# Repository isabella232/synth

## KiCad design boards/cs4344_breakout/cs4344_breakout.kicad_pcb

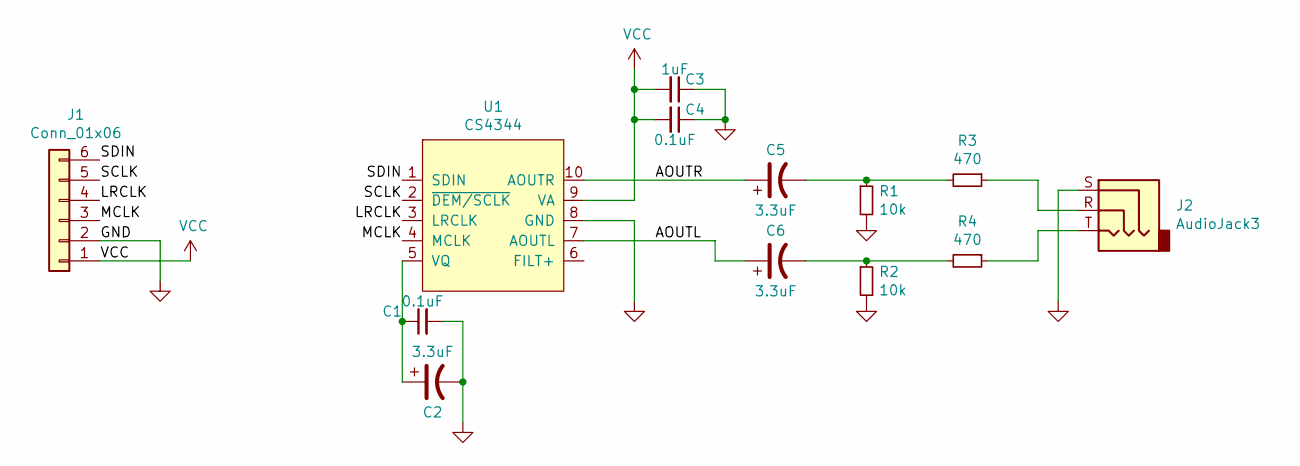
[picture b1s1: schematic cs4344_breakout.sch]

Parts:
C1, C4: 0.1uF; C_0603_1608Metric_Pad1.05x0.95mm_HandSolder
C2, C5, C6: 3.3uF; CP_EIA-1608-08_AVX-J_Pad1.25x1.05mm_HandSolder
C3: 1uF; C_0603_1608Metric_Pad1.05x0.95mm_HandSolder
J1: Conn_01x06; PinHeader_1x06_P2.54mm_Vertical
J2: AudioJack3; Jack_3.5mm_CUI_SJ-3523-SMT_Horizontal
R1, R2: 10k; R_0603_1608Metric_Pad1.05x0.95mm_HandSolder
R3, R4: 470; R_0603_1608Metric_Pad1.05x0.95mm_HandSolder
U1: CS4344; TSSOP-10_3x3mm_P0.5mm

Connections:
/AOUTL: C6.1, U1.7 (AOUTL)
/AOUTR: C5.1, U1.10 (AOUTR)
/LRCLK: J1.4, U1.3 (LRCLK)
/MCLK: J1.3, U1.4 (MCLK)
/SCLK: J1.5, U1.2 (~DEM/SCLK)
/SDIN: J1.6, U1.1 (SDIN)
GND: C1.2, C2.2, C3.1, C4.1, J1.2, J2.S, R1.2, R2.2, U1.8 (GND)
unnamed: C1.1, C2.1, U1.5 (VQ)
unnamed: C5.2, R1.1, R3.2
unnamed: C6.2, R2.1, R4.2
unnamed: J2.R, R3.1
unnamed: J2.T, R4.1
VCC: C3.2, C4.2, J1.1, U1.9 (VA)

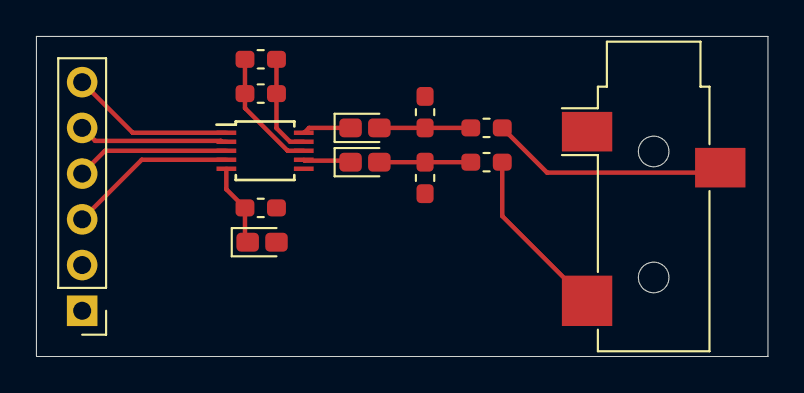
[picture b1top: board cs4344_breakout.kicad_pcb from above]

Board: 2 copper layers, 40.6 x 17.8 mm, 13 parts (0 on the bottom side), 13 nets.

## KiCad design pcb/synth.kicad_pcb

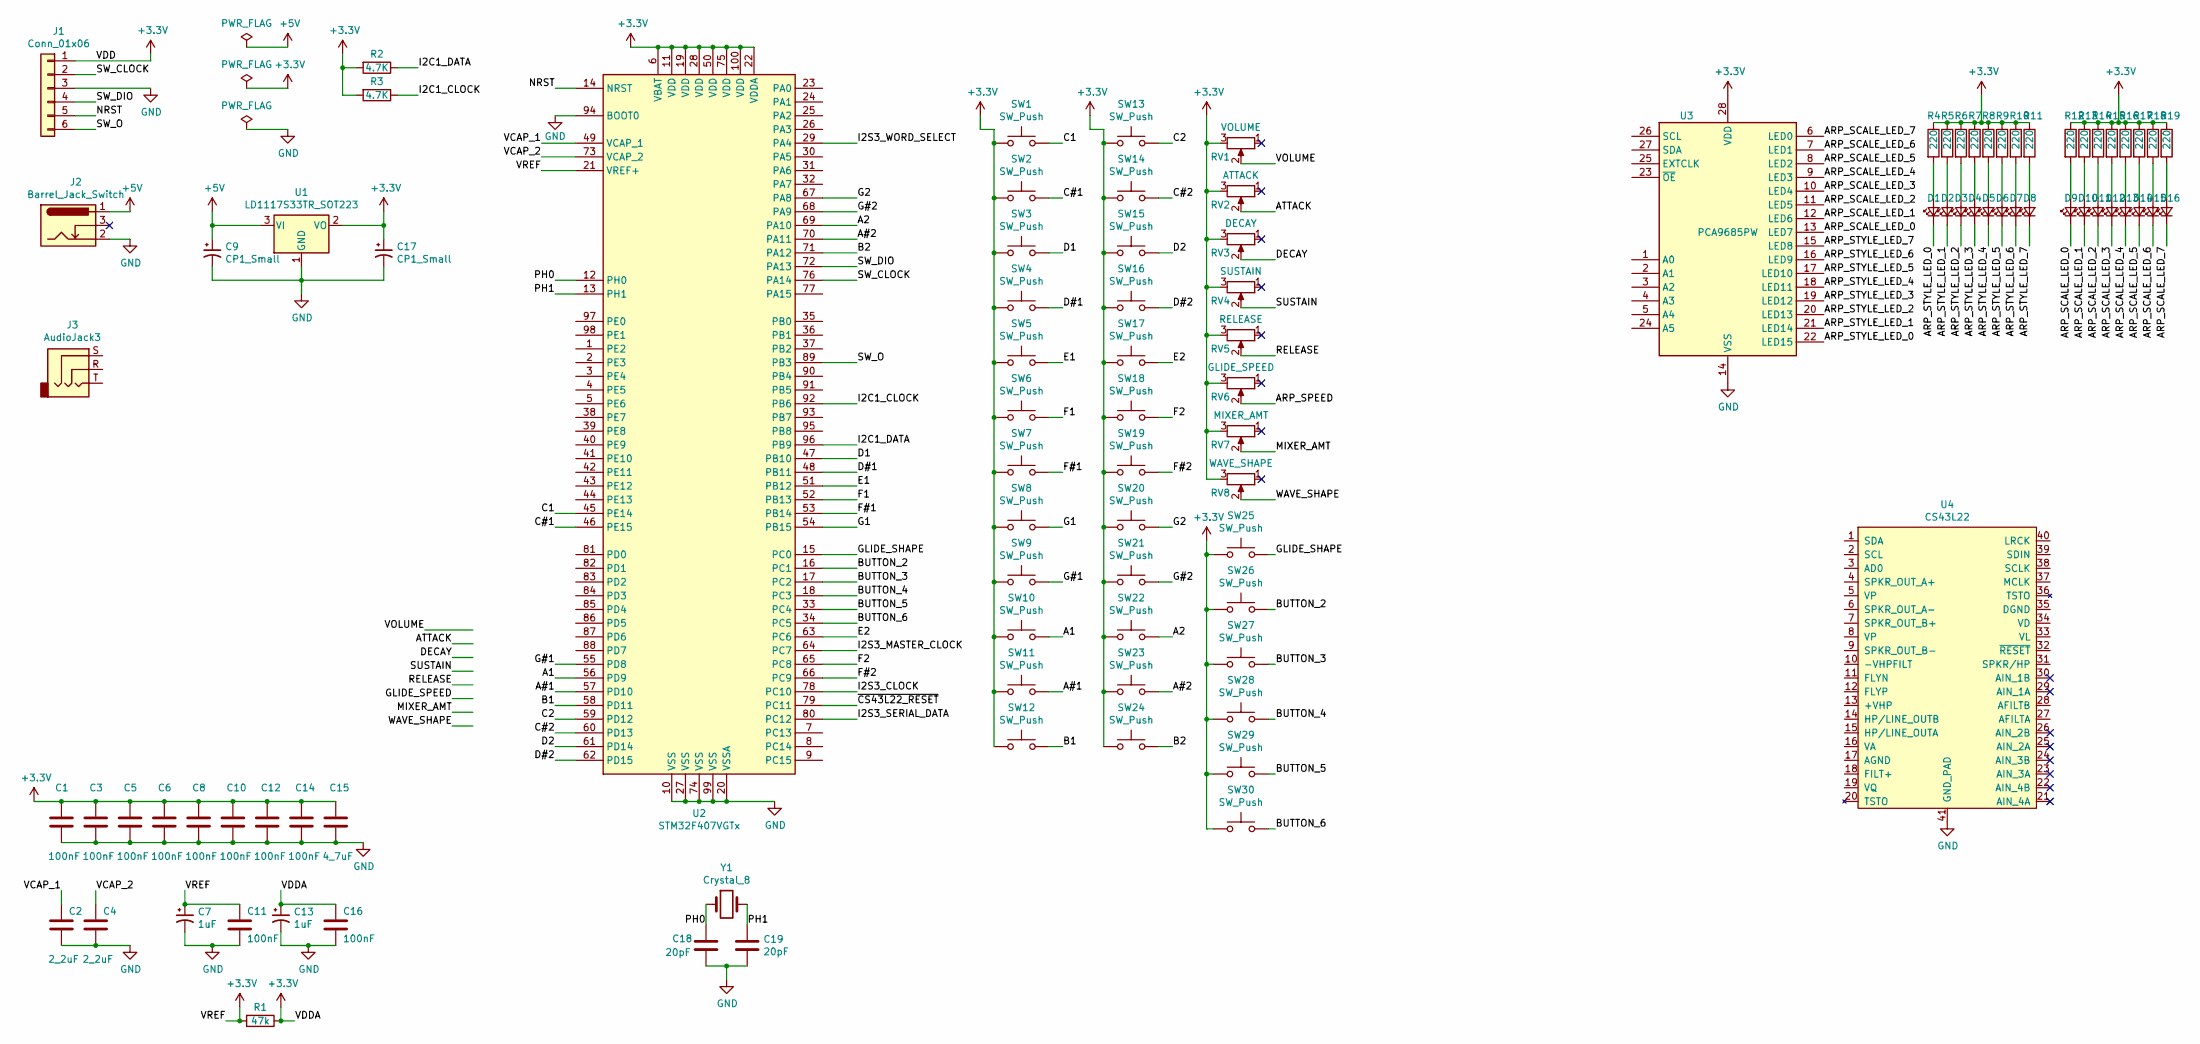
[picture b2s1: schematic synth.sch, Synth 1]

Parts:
C1, C3, C5, C6, C8, C10, C11, C12, C14, C16: 100nF; C_Disc_D3.0mm_W2.0mm_P2.50mm
C2, C4: 2_2uF; C_Disc_D3.0mm_W2.0mm_P2.50mm
C7, C13: 1uF; C_Disc_D3.0mm_W2.0mm_P2.50mm
C9, C17: CP1_Small
C15: 4_7uF; C_Disc_D3.0mm_W2.0mm_P2.50mm
C18, C19: 20pF; C_Disc_D3.0mm_W2.0mm_P2.50mm
D1, D2, D3, D4, D5, D6, D7, D8, D9, D10, D11, D12, D13, D14, D15, D16: LED_Small; LED_0805_2012Metric
J1: Conn_01x06; PinHeader_1x06_P2.54mm_Vertical
J2: Barrel_Jack_Switch; BarrelJack_CUI_PJ-063AH_Horizontal
J3: AudioJack3; Jack_3.5mm_CUI_SJ1-3533NG_Horizontal
R1: 47k
R2, R3: 4.7K; R_Axial_DIN0204_L3.6mm_D1.6mm_P5.08mm_Horizontal
R4, R5, R6, R7, R8, R9, R10, R11, R12, R13, R14, R15, R16, R17, R18, R19: 220; R_0805_2012Metric
RV1: VOLUME; Potentiometer_Bourns_PTV09A-1_Single_Vertical
RV2: ATTACK; Potentiometer_Bourns_PTV09A-1_Single_Vertical
RV3: DECAY; Potentiometer_Bourns_PTV09A-1_Single_Vertical
RV4: SUSTAIN; Potentiometer_Bourns_PTV09A-1_Single_Vertical
RV5: RELEASE; Potentiometer_Bourns_PTV09A-1_Single_Vertical
RV6: GLIDE_SPEED; Potentiometer_Bourns_PTV09A-1_Single_Vertical
RV7: MIXER_AMT; Potentiometer_Bourns_PTV09A-1_Single_Vertical
RV8: WAVE_SHAPE; Potentiometer_Bourns_PTV09A-1_Single_Vertical
SW1, SW2, SW3, SW4, SW5, SW6, SW7, SW8, SW9, SW10, SW11, SW12, SW13, SW14, SW15, SW16, SW17, SW18, SW19, SW20, SW21, SW22, SW23, SW24, SW25, SW26, SW27, SW28, SW29, SW30: SW_Push; Mountain Switch Narrow
U1: LD1117S33TR_SOT223; SOT-223-3_TabPin2
U2: STM32F407VGTx; LQFP-100_14x14mm_P0.5mm
U3: PCA9685PW; TSSOP-28_4.4x9.7mm_P0.65mm
U4: CS43L22; QFN-40-1EP_6x6mm_P0.5mm_EP4.6x4.6mm
Y1: Crystal_8; ATS08A

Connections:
+3V3: C1.1, C3.1, C5.1, C6.1, C7.1, C8.1, C10.1, C11.1, C12.1, C13.1, C14.1, C15.1, C16.1, C17.1, J1.1, R1.1, R1.2, R2.2, R3.2, R4.1, R5.1, R6.1, R7.1, R8.1, R9.1, R10.1, R11.1, R12.1, R13.1, R14.1, R15.1, R16.1, R17.1, R18.1, R19.1, RV1.3, RV2.3, RV3.3, RV4.3, RV5.3, RV6.3, RV7.3, RV8.3, SW1.1, SW2.1, SW3.1, SW4.1, SW5.1, SW6.1, SW7.1, SW8.1, SW9.1, SW10.1, SW11.1, SW12.1, SW13.1, SW14.1, SW15.1, SW16.1, SW17.1, SW18.1, SW19.1, SW20.1, SW21.1, SW22.1, SW23.1, SW24.1, SW25.1, SW26.1, SW27.1, SW28.1, SW29.1, SW30.1, U1.2 (VO), U2.6 (VBAT), U2.11 (VDD), U2.19 (VDD), U2.21 (VREF+), U2.22 (VDDA), U2.28 (VDD), U2.50 (VDD), U2.75 (VDD), U2.100 (VDD), U3.28 (VDD)
+5V: C9.1, J2.1, U1.3 (VI)
/A1: SW10.2, U2.56 (PD9)
/A2: SW22.2, U2.69 (PA10)
/A#1: SW11.2, U2.57 (PD10)
/A#2: SW23.2, U2.70 (PA11)
/ARP_SCALE_LED_0: D9.1 (K), U3.13 (LED7)
/ARP_SCALE_LED_1: D10.1 (K), U3.12 (LED6)
/ARP_SCALE_LED_2: D11.1 (K), U3.11 (LED5)
/ARP_SCALE_LED_3: D12.1 (K), U3.10 (LED4)
/ARP_SCALE_LED_4: D13.1 (K), U3.9 (LED3)
/ARP_SCALE_LED_5: D14.1 (K), U3.8 (LED2)
/ARP_SCALE_LED_6: D15.1 (K), U3.7 (LED1)
/ARP_SCALE_LED_7: D16.1 (K), U3.6 (LED0)
/ARP_SPEED: RV6.2
/ARP_STYLE_LED_0: D1.1 (K), U3.22 (LED15)
/ARP_STYLE_LED_1: D2.1 (K), U3.21 (LED14)
/ARP_STYLE_LED_2: D3.1 (K), U3.20 (LED13)
/ARP_STYLE_LED_3: D4.1 (K), U3.19 (LED12)
/ARP_STYLE_LED_4: D5.1 (K), U3.18 (LED11)
/ARP_STYLE_LED_5: D6.1 (K), U3.17 (LED10)
/ARP_STYLE_LED_6: D7.1 (K), U3.16 (LED9)
/ARP_STYLE_LED_7: D8.1 (K), U3.15 (LED8)
/ATTACK: RV2.2
/B1: SW12.2, U2.58 (PD11)
/B2: SW24.2, U2.71 (PA12)
/BUTTON_2: SW26.2, U2.16 (PC1)
/BUTTON_3: SW27.2, U2.17 (PC2)
/BUTTON_4: SW28.2, U2.18 (PC3)
/BUTTON_5: SW29.2, U2.33 (PC4)
/BUTTON_6: SW30.2, U2.34 (PC5)
/C1: SW1.2, U2.45 (PE14)
/C2: SW13.2, U2.59 (PD12)
/C#1: SW2.2, U2.46 (PE15)
/C#2: SW14.2, U2.60 (PD13)
/D1: SW3.2, U2.47 (PB10)
/D2: SW15.2, U2.61 (PD14)
/D#1: SW4.2, U2.48 (PB11)
/D#2: SW16.2, U2.62 (PD15)
/DECAY: RV3.2
/E1: SW5.2, U2.51 (PB12)
/E2: SW17.2, U2.63 (PC6)
/F1: SW6.2, U2.52 (PB13)
/F2: SW18.2, U2.65 (PC8)
/F#1: SW7.2, U2.53 (PB14)
/F#2: SW19.2, U2.66 (PC9)
/G1: SW8.2, U2.54 (PB15)
/G2: SW20.2, U2.67 (PA8)
/G#1: SW9.2, U2.55 (PD8)
/G#2: SW21.2, U2.68 (PA9)
/GLIDE_SHAPE: SW25.2, U2.15 (PC0)
/I2C1_CLOCK: R3.1, U2.92 (PB6)
/I2C1_DATA: R2.1, U2.96 (PB9)
/I2S3_CLOCK: U2.78 (PC10)
/I2S3_MASTER_CLOCK: U2.64 (PC7)
/I2S3_SERIAL_DATA: U2.80 (PC12)
/I2S3_WORD_SELECT: U2.29 (PA4)
/MIXER_AMT: RV7.2
/NRST: J1.5, U2.14 (NRST)
/PH0: C18.1, U2.12 (PH0), Y1.1
/PH1: C19.1, U2.13 (PH1), Y1.2
/RELEASE: RV5.2
/SUSTAIN: RV4.2
/SW_CLOCK: J1.2, U2.76 (PA14)
/SW_DIO: J1.4, U2.72 (PA13)
/SW_O: J1.6, U2.89 (PB3)
/VCAP_1: C2.1, U2.49 (VCAP_1)
/VCAP_2: C4.1, U2.73 (VCAP_2)
/VOLUME: RV1.2
/WAVE_SHAPE: RV8.2
/~CS43L22_RESET: U2.79 (PC11)
GND: C1.2, C2.2, C3.2, C4.2, C5.2, C6.2, C7.2, C8.2, C9.2, C10.2, C11.2, C12.2, C13.2, C14.2, C15.2, C16.2, C17.2, C18.2, C19.2, J1.3, J2.2, U1.1 (GND), U2.10 (VSS), U2.20 (VSSA), U2.27 (VSS), U2.74 (VSS), U2.94 (BOOT0), U2.99 (VSS), U3.14 (VSS), U4.41 (GND_PAD)
unnamed: D1.2 (A), R4.2
unnamed: D2.2 (A), R5.2
unnamed: D3.2 (A), R6.2
unnamed: D4.2 (A), R7.2
unnamed: D5.2 (A), R8.2
unnamed: D6.2 (A), R9.2
unnamed: D7.2 (A), R10.2
unnamed: D8.2 (A), R11.2
unnamed: D9.2 (A), R12.2
unnamed: D10.2 (A), R13.2
unnamed: D11.2 (A), R14.2
unnamed: D12.2 (A), R15.2
unnamed: D13.2 (A), R16.2
unnamed: D14.2 (A), R17.2
unnamed: D15.2 (A), R18.2
unnamed: D16.2 (A), R19.2

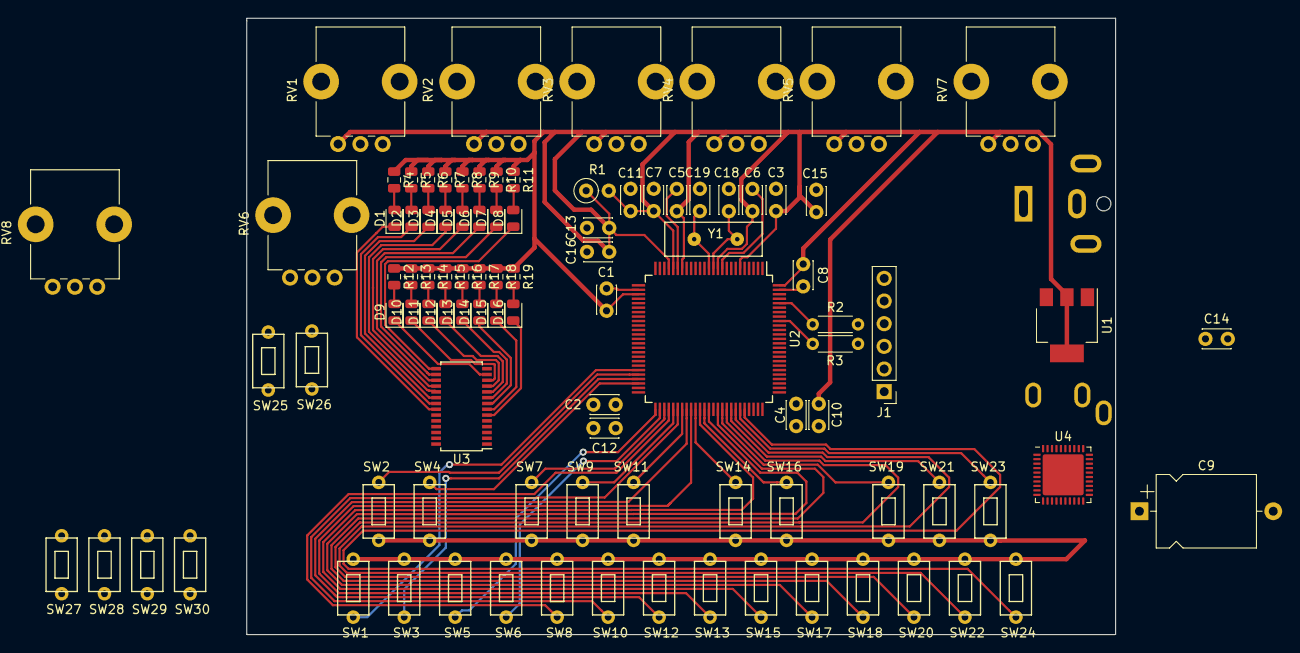
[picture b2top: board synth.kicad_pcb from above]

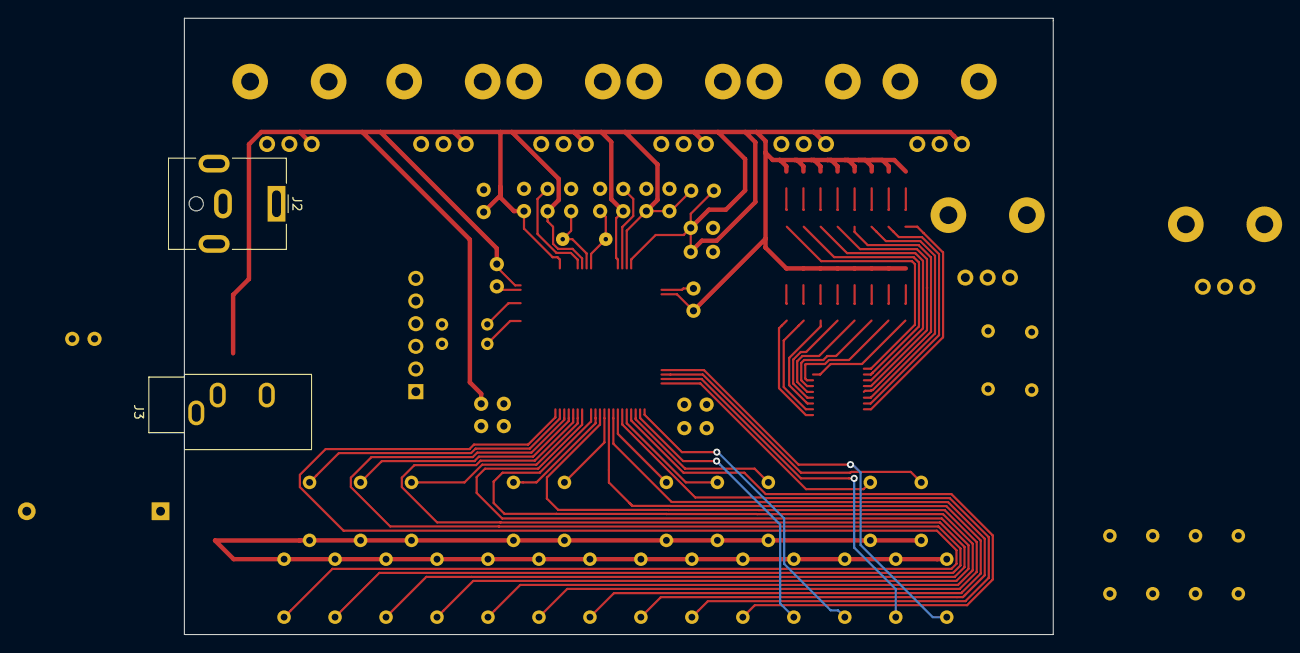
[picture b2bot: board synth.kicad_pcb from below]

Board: 2 copper layers, 97.4 x 69.1 mm, 99 parts (2 on the bottom side), 75 nets.

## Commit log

2018-12-27 Add a Python script to generate sine wave tables.
2018-12-27 Add a wavetable based oscillator.
2018-12-27 Add a 2-channel mixer with saturating arithmetic.
2018-12-27 Add a simple 16.16 fixed math library.
2018-12-28 Add a basic envelope. It has fixed point resolution issues for long durations.
2018-12-28 Fix precision issues with envelopes.
    Step sizes are now scaled from 0 to UINT16_MAX as opposed to 0 to 1.
    This gives us maximum precision on step size.
2018-12-31 Fix an multiplication overflow bug in fixed math.
    When multiplying two numbers together that were both > 1, we'd overflow
    the available 16 bits of integer available.
    I'm not sure this is the best way around it, but for now I chop off 8
    bits of fractional precision in the case that both numbers are > 1.
    It's much less precise but better than totally wrong.
2018-12-31 Add a test footprint for a 1-octave keyboard.
2019-01-02 Fix two bugs relating to sustain levels.
    The first bug was not modulating the input sample by the sustain level.
    The second was accidentally returning the unmodulated sustain level
    during the first sustain sample.
2019-01-02 Add a missing Fixed1616AsInt.
2019-01-02 Round samples for better accuracy.
2019-01-02 Remove unused debugging function.
2019-01-02 Fix a bug with oscillator increment computation.
2019-01-04 Add generation of sawtooth waves.
2019-01-04 Add linear interpolation to the oscillator.
2019-01-04 Optimize oscillator by using uint8_t rollover.
    Because we know the wavetable size is 256, when asking for the table
    index following the current one we can store the index as a uint8_t and
    allow integer overflow to do the mod 256 for us.
    This saves a few instructions.
2019-01-04 Remove no-longer needed mod 255.
2019-01-04 Remove left over #includes.
2019-01-05 Add a sequencer.
    The sequencer supports a configurable number of steps and pulse width.
2019-01-05 Fix an off-by-one bug in the sequencer.
    Moving where we increment the counter changed the handling of size 1
    pulse widths.
2019-01-08 Add a basic CS43L22 driver.
2019-01-08 Move synth library into its own folder.
2019-01-08 Move defines.h to synth folder as well. It got left out.
2019-01-08 Replace tabs with spaces thanks to fixed vimrc.
2019-01-08 Move wavetable generation script to the synth dir.
2019-01-08 Add generated wavetables.
2019-01-08 Remove early returns.
    Same results as before. Just makes all cases consistent.
2019-01-17 Fix C function naming style.
2019-01-19 Add some basic easing functions.
2019-01-19 Add an untested interpolator that uses easing functions.
2019-01-20 Remove .lib from .gitignore because it's used by KiCad.
2019-01-20 Add an early schematic for the synth.
    Very little done so far, except placing labels for I2S, I2C, creating
    the keyboard, adding the crystal, and attempting the programming interface
    but probably not succeeding yet.
2019-01-20 Add a bunch of decoupling caps, and populate VCAP_{1,2}.
2019-01-20 Add a 4.7 uF cap as per page 77 of datasheet.
    https://www.st.com/resource/en/datasheet/stm32f405og.pdf
2019-01-21 Add potentiometer knobs.
    This includes volume, A, D, S, R, glide speed, and mixer amount.
2019-01-21 Clean up knobs and add a wave shape knob.
2019-01-21 Add cap values for the crystal caps, and mark unused pot legs as NC.
2019-01-21 Fix a not connected sustain knob.
2019-01-21 Add power flags and update the crystal to be 8 MHz.
2019-01-21 Add i2c pullup resistors.
2019-01-22 Add the STM32CubeMX file for the discovery board version.
2019-01-26 Add more buttons, and connect SWD VDD to 3.3V.
    Also set some cap and resistor values.
2019-01-27 Add voltage regulator, barrel jack.
    Also associated somewhat arbitrary footprints with components.
2019-01-27 Add microcontroller to BOM.
2019-01-27 Hook up VREF to ground through a 1uF and .1uF cap.
2019-01-27 Connect the VREF pin to the VREF net.
2019-01-27 Decouple VDDA similar to VREF, and connect both to VDD.
2019-01-27 Add a custom schematic and footprint library.
2019-01-27 Add an early 100x100mm PCB layout.
    Route some power to buttons.
2019-01-28 A bunch of routing and footprint changes.
2019-01-28 Add a footprint for the ATS08A 8 MHz crystal.
2019-02-02 Add a new potentiometer candidate.
2019-02-04 A ton of changes.
    - Redid the routing for the keyboard.
    - Added LEDs for Arp style and scale with accompanying driver.
2019-02-06 Fix link for headphone jack.
2019-02-06 Switch headphone jack to CUI SJ1-3533NG since it's in KiCad already.
2019-02-06 Add CS43L22 audio DAC.
2019-02-06 Create a schematic for the CS43L22 DAC.
2019-02-09 Add a WIP STM32f4 main.
2019-02-10 Include a new DAC that looks like a better and easier fit.
2019-02-11 Add a schematic for the TLV320DAC26 DAC.
2019-02-16 Add about half of the schematic for the CS43L22 DAC.
2020-07-05 Add vim .swp files to gitignore.
2020-07-05 Begin implementing block based audio generation by introducing AudioBlock.
2020-07-05 Add an AudioProcessor which fills and propagates audio blocks.
2020-07-11 Create notes.md
    Include links to two articles.
2020-07-12 Add TLV320DAC32 to DAC candidate list
2020-07-20 Add the CS4344 DAC that I'll likely use.
2020-07-20 Move pcb directory to a new name.
2020-07-20 Add CS4344 DAC to kicad libs.
2020-07-20 Start a CS4344 breakout board.
2021-06-14 [ImgBot] Optimize images
    *Total -- 514.64kb -> 467.49kb (9.16%)
    /sketches/keyboard_test_1.svg -- 123.85kb -> 91.96kb (25.76%)
    /boards/cs4344_breakout/cs4344_breakout.png -- 390.78kb -> 375.54kb (3.9%)
